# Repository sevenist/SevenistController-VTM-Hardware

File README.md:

# Sevenist Controller — Hardware (VTM)

Custom PCB for the **Sevenist Controller**, a 64-track MIDI CC control surface built around an [ESP32-S3 Zero](https://docs.waveshare.com/ESP32-S3-Zero).

This repository holds the KiCad project, schematics and fabrication files for the board. The code for it : [VTM Firmware repository](https://github.com/sevenist/SevenistController-VTM-Firmware).

> **Status: updated, should work but not tested yet. will upload soon some BOM file.**
> Fabricate at your own risk until it's confirmed working.

## Repository layout

```
relControll.kicad_pro / .kicad_sch / .kicad_pcb   KiCad 10 project, schematic, board
images/                                            Board renders
```

## License

Released under the [GPL-3.0](LICENSE) license.

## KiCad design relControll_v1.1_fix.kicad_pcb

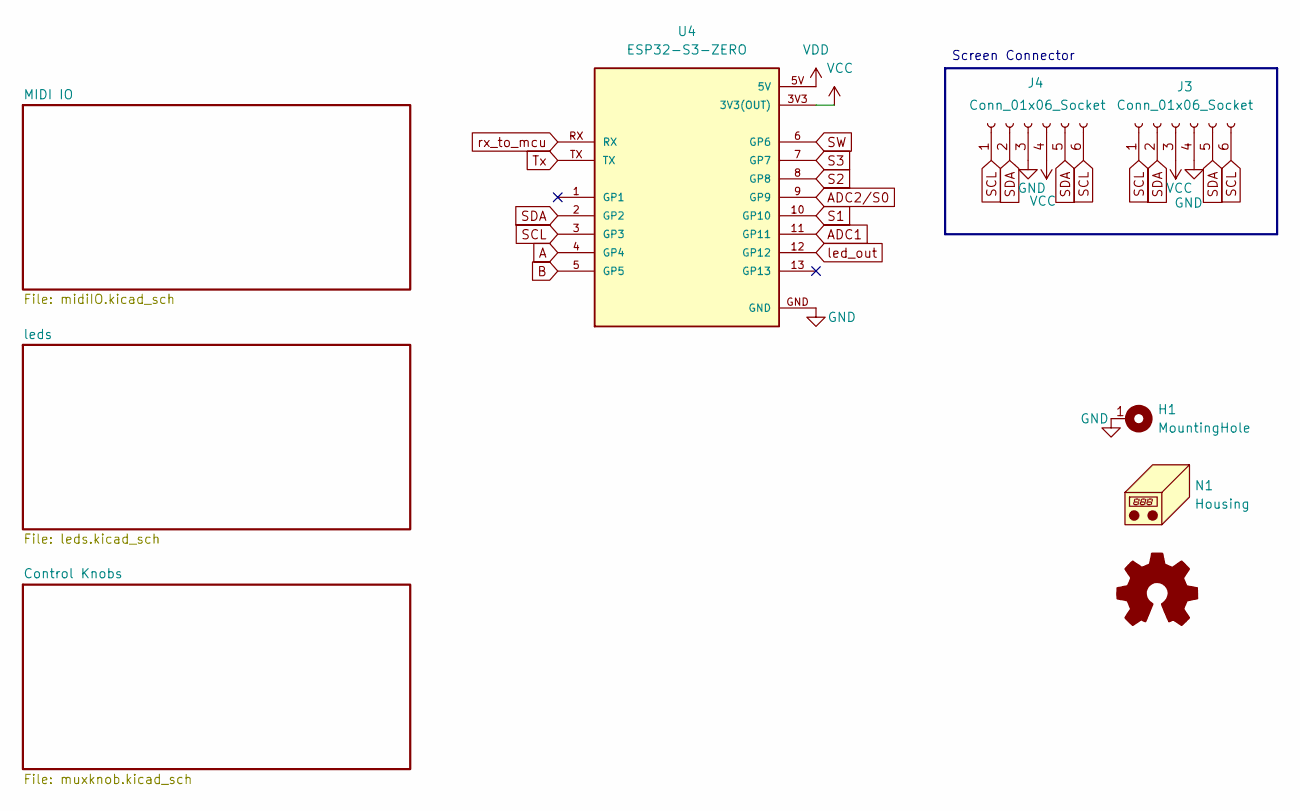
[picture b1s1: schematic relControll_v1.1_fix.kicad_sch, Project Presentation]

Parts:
H1: MountingHole; MountingHole_2.7mm_M2.5_ISO14580_Pad
J3, J4: Conn_01x06_Socket; PinSocket_1x06_P2.54mm_Vertical
N1: Housing; Screw_Generic_2.0x3.0mm_SilkScreen
U4: ESP32-S3-ZERO; MODULE_ESP32-S3-ZERO; PARTREV NA

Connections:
A: U4.4 (GP4); also elsewhere on the board
ADC1: U4.11 (GP11); also elsewhere on the board
ADC2/S0: U4.9 (GP9); also elsewhere on the board
B: U4.5 (GP5); also elsewhere on the board
GND: H1.1, J3.4, J4.3, U4.GND; also elsewhere on the board
S1: U4.10 (GP10); also elsewhere on the board
S2: U4.8 (GP8); also elsewhere on the board
S3: U4.7 (GP7); also elsewhere on the board
SCL: J3.1, J3.6, J4.1, J4.6, U4.3 (GP3)
SDA: J3.2, J3.5, J4.2, J4.5, U4.2 (GP2)
SW: U4.6 (GP6); also elsewhere on the board
Tx: U4.TX; also elsewhere on the board
VCC: J3.3, J4.4, U4.3V3 (3V3(OUT)); also elsewhere on the board
VDD: U4.5V; also elsewhere on the board
led_out: U4.12 (GP12); also elsewhere on the board
rx_to_mcu: U4.RX; also elsewhere on the board

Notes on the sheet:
Screen Connector

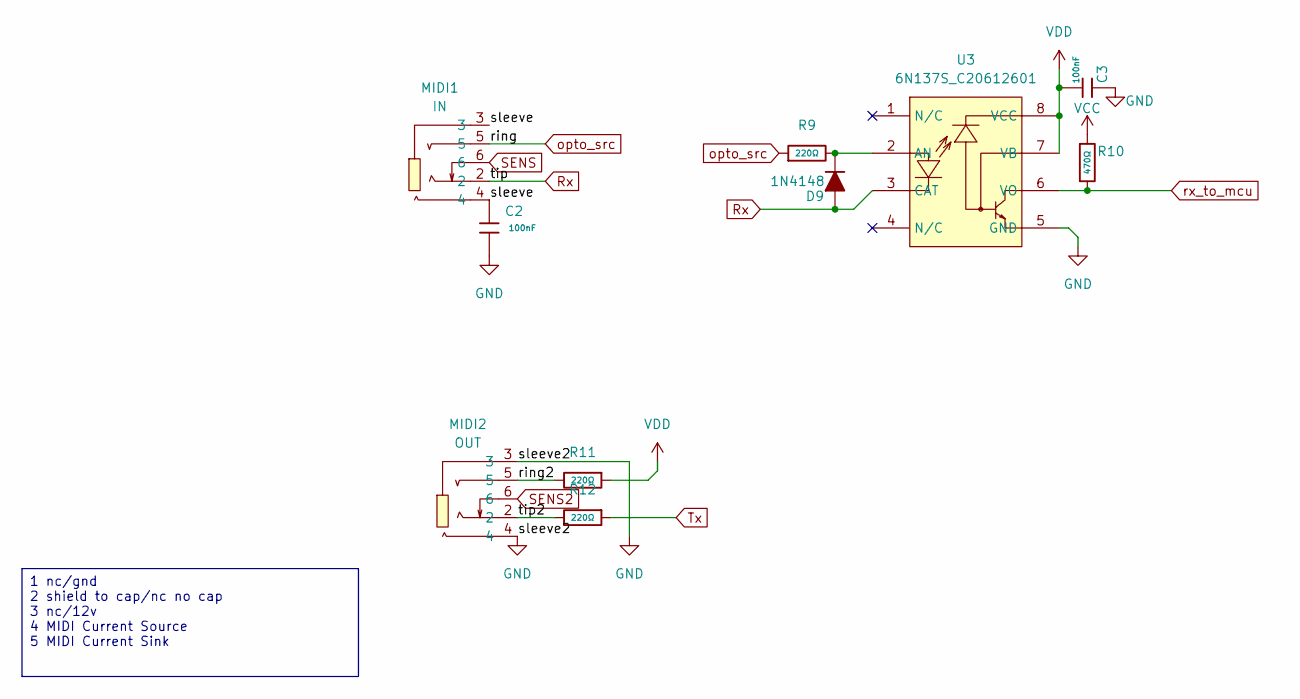
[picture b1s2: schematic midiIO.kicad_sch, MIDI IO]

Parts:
C2, C3: 100nF; C_0805; Voltage Rated 50V; Tolerance ±10%; Part CC0805KRX7R9BB104; LCSC C49678
D9: 1N4148; D_SOD123_axial
MIDI1: IN; AUDIO-TH_PJ-3270; MPN PJ-3270; LCSC Part C381134
MIDI2: OUT; AUDIO-TH_PJ-3270; MPN PJ-3270; LCSC Part C381134
R9, R11, R12: 220Ω; R_0805; Overload Voltage (Max) 150V; Tolerance ±1%; Part 0805W8F2200T5E; LCSC C17557
R10: 470Ω; R_0805; Overload Voltage (Max) 150V; Tolerance ±1%; Part 0805W8F4700T5E; LCSC C17710
U3: 6N137S_C20612601; SOP-8_6.605x9.655mm_P2.54mm; MPN 6N137S; LCSC Part C20612601

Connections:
/MIDI IO/ring2: MIDI2.5, R11.2
/MIDI IO/sleeve: C2.1, MIDI1.3, MIDI1.4
/MIDI IO/tip2: MIDI2.2, R12.2
GND: C2.2, C3.2, MIDI2.3, MIDI2.4, U3.5 (GND); also elsewhere on the board
unnamed: D9.1 (K), R9.2, U3.2 (AN)
Rx: D9.2 (A), MIDI1.2, U3.3 (CAT)
SENS: MIDI1.6
SENS2: MIDI2.6
Tx: R12.1; also elsewhere on the board
VCC: R10.1; also elsewhere on the board
VDD: C3.1, R11.1, U3.7 (VB), U3.8 (VCC); also elsewhere on the board
opto_src: MIDI1.5, R9.1
rx_to_mcu: R10.2, U3.6 (VO); also elsewhere on the board

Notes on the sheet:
1 nc/gnd 2 shield to cap/nc no cap 3 nc/12v 4 MIDI Current Source 5 MIDI Current Sink

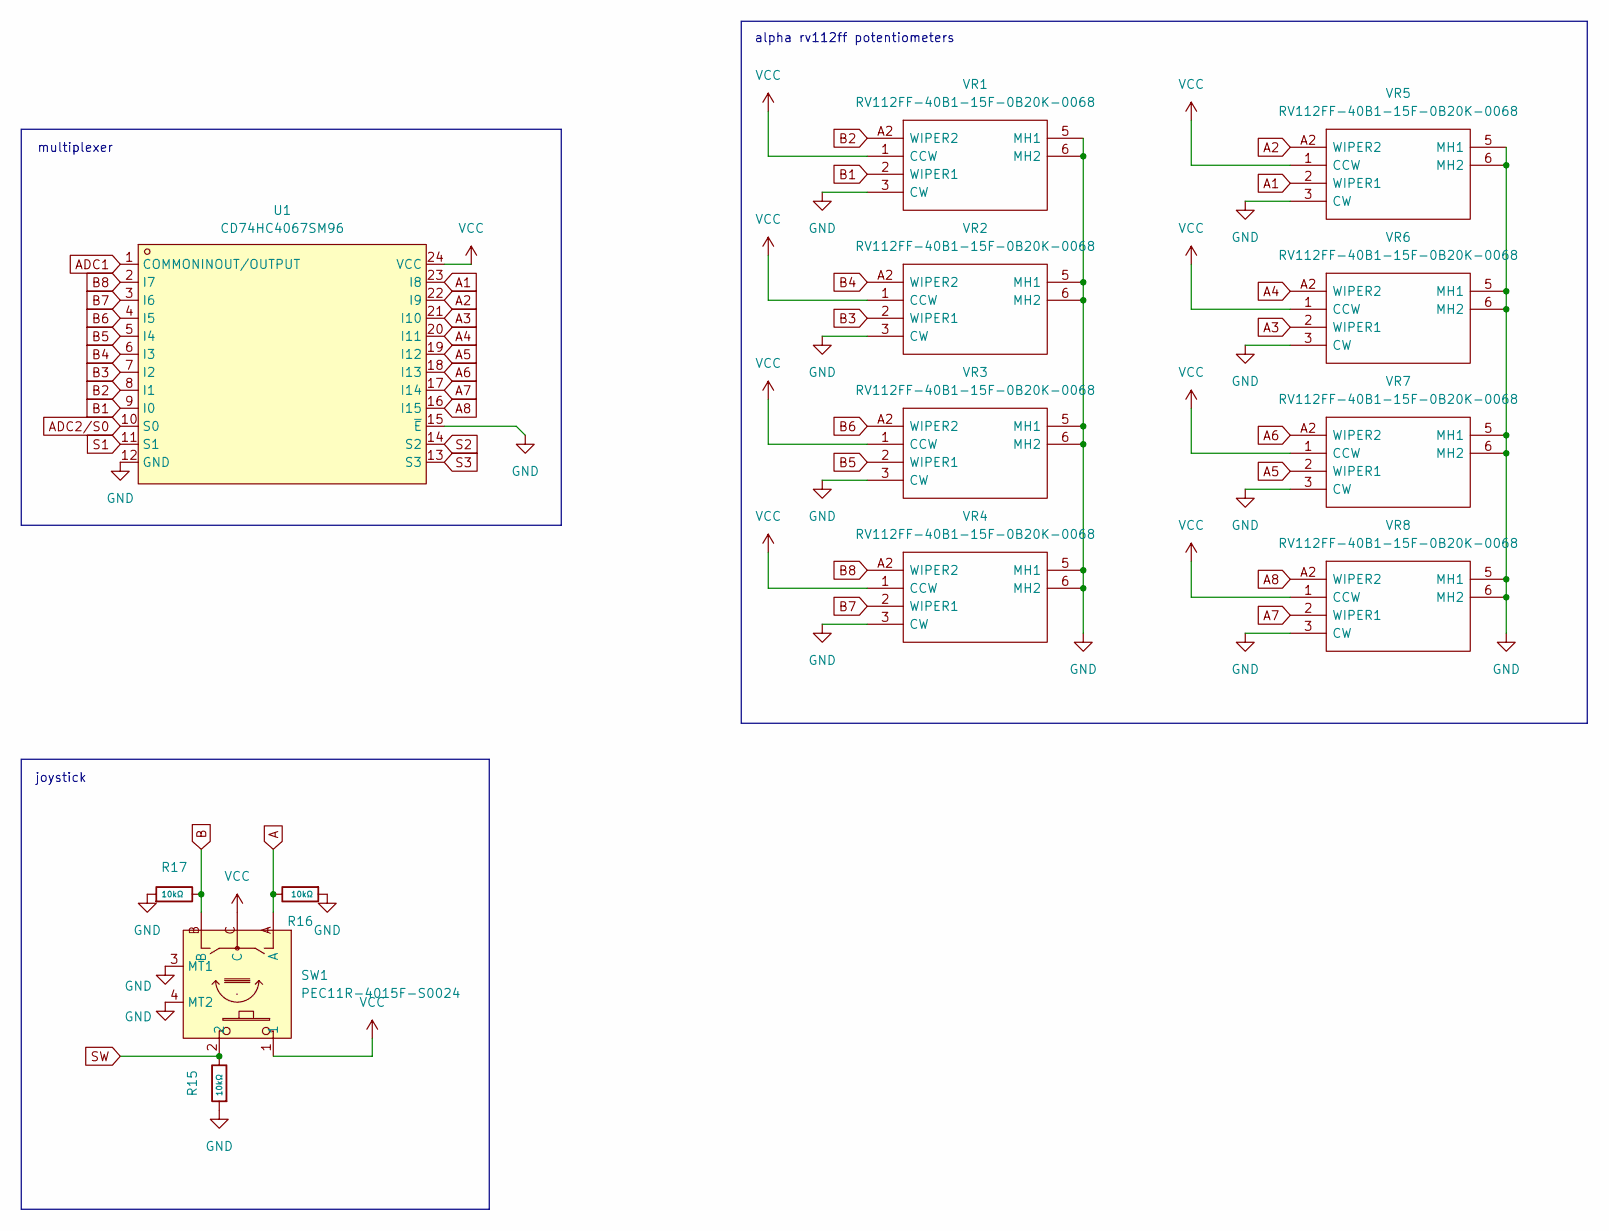
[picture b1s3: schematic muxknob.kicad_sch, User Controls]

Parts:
R15: 10kΩ; R0805; Overload Voltage (Max) 150V; Tolerance ±1%; Part 0805W8F1002T5E; LCSC C17414
R16, R17: 10kΩ; R_0805; Overload Voltage (Max) 150V; Tolerance ±1%; Part 0805W8F1002T5E; LCSC C17414
SW1: PEC11R-4015F-S0024; SW-TH_PEC12R-4130F-S0012; MPN PEC11R-4015F-S0024; LCSC Part C143789
U1: CD74HC4067SM96; SSOP-24_L8.1-W5.3-P0.65-LS7.8-BL; MPN CD74HC4067SM96; LCSC Part C98457
VR1, VR2, VR3, VR4, VR5, VR6, VR7, VR8: RV112FF-40B1-15F-0B20K-0068; RV112FF40B115F0B20K0068; Mouser Part Number 317-1240FF-15F-0B20K

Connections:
A: R16.2, SW1.A; also elsewhere on the board
A1: U1.23 (I8), VR5.2 (WIPER1)
A2: U1.22 (I9), VR5.A2 (WIPER2)
A3: U1.21 (I10), VR6.2 (WIPER1)
A4: U1.20 (I11), VR6.A2 (WIPER2)
A5: U1.19 (I12), VR7.2 (WIPER1)
A6: U1.18 (I13), VR7.A2 (WIPER2)
A7: U1.17 (I14), VR8.2 (WIPER1)
A8: U1.16 (I15), VR8.A2 (WIPER2)
ADC1: U1.1 (COMMONINOUT/OUTPUT); also elsewhere on the board
ADC2/S0: U1.10 (S0); also elsewhere on the board
B: R17.2, SW1.B; also elsewhere on the board
B1: U1.9 (I0), VR1.2 (WIPER1)
B2: U1.8 (I1), VR1.A2 (WIPER2)
B3: U1.7 (I2), VR2.2 (WIPER1)
B4: U1.6 (I3), VR2.A2 (WIPER2)
B5: U1.5 (I4), VR3.2 (WIPER1)
B6: U1.4 (I5), VR3.A2 (WIPER2)
B7: U1.3 (I6), VR4.2 (WIPER1)
B8: U1.2 (I7), VR4.A2 (WIPER2)
GND: R15.1, R16.1, R17.1, SW1.3 (MT1), SW1.4 (MT2), U1.12 (GND), U1.15 (~E), VR1.3 (CW), VR1.5 (MH1), VR1.6 (MH2), VR2.3 (CW), VR2.5 (MH1), VR2.6 (MH2), VR3.3 (CW), VR3.5 (MH1), VR3.6 (MH2), VR4.3 (CW), VR4.5 (MH1), VR4.6 (MH2), VR5.3 (CW), VR5.5 (MH1), VR5.6 (MH2), VR6.3 (CW), VR6.5 (MH1), VR6.6 (MH2), VR7.3 (CW), VR7.5 (MH1), VR7.6 (MH2), VR8.3 (CW), VR8.5 (MH1), VR8.6 (MH2); also elsewhere on the board
S1: U1.11 (S1); also elsewhere on the board
S2: U1.14 (S2); also elsewhere on the board
S3: U1.13 (S3); also elsewhere on the board
SW: R15.2, SW1.2; also elsewhere on the board
VCC: SW1.1, SW1.C, U1.24 (VCC), VR1.1 (CCW), VR2.1 (CCW), VR3.1 (CCW), VR4.1 (CCW), VR5.1 (CCW), VR6.1 (CCW), VR7.1 (CCW), VR8.1 (CCW); also elsewhere on the board

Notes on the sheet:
alpha rv112ff potentiometers
joystick
multiplexer

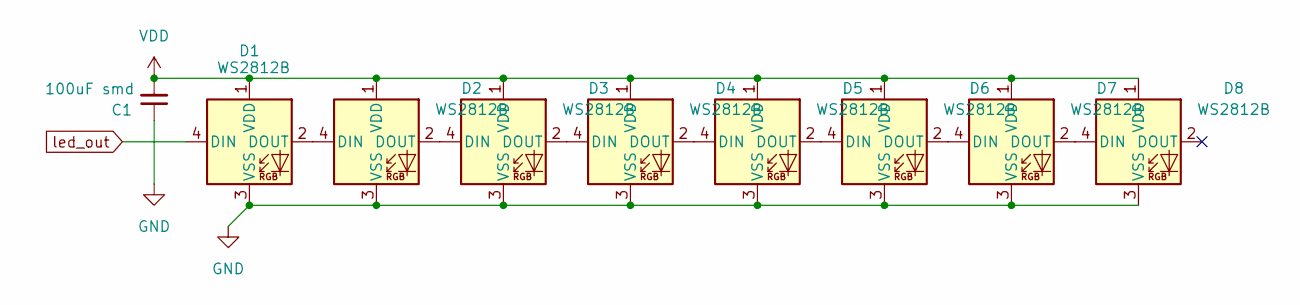
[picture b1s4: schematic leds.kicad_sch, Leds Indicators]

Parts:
C1: 100uF smd; C_Elec_6.3x5.4
D1, D2, D3, D4, D5, D6, D7, D8: WS2812B; LED_WS2812B_PLCC4_5.0x5.0mm_P3.2mm; LCSC C22461793

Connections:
GND: C1.1, D1.3 (VSS), D2.3 (VSS), D3.3 (VSS), D4.3 (VSS), D5.3 (VSS), D6.3 (VSS), D7.3 (VSS), D8.3 (VSS); also elsewhere on the board
unnamed: D1.2 (DOUT), D2.4 (DIN)
unnamed: D2.2 (DOUT), D3.4 (DIN)
unnamed: D3.2 (DOUT), D4.4 (DIN)
unnamed: D4.2 (DOUT), D5.4 (DIN)
unnamed: D5.2 (DOUT), D6.4 (DIN)
unnamed: D6.2 (DOUT), D7.4 (DIN)
unnamed: D7.2 (DOUT), D8.4 (DIN)
VDD: C1.2, D1.1 (VDD), D2.1 (VDD), D3.1 (VDD), D4.1 (VDD), D5.1 (VDD), D6.1 (VDD), D7.1 (VDD), D8.1 (VDD); also elsewhere on the board
led_out: D1.4 (DIN); also elsewhere on the board

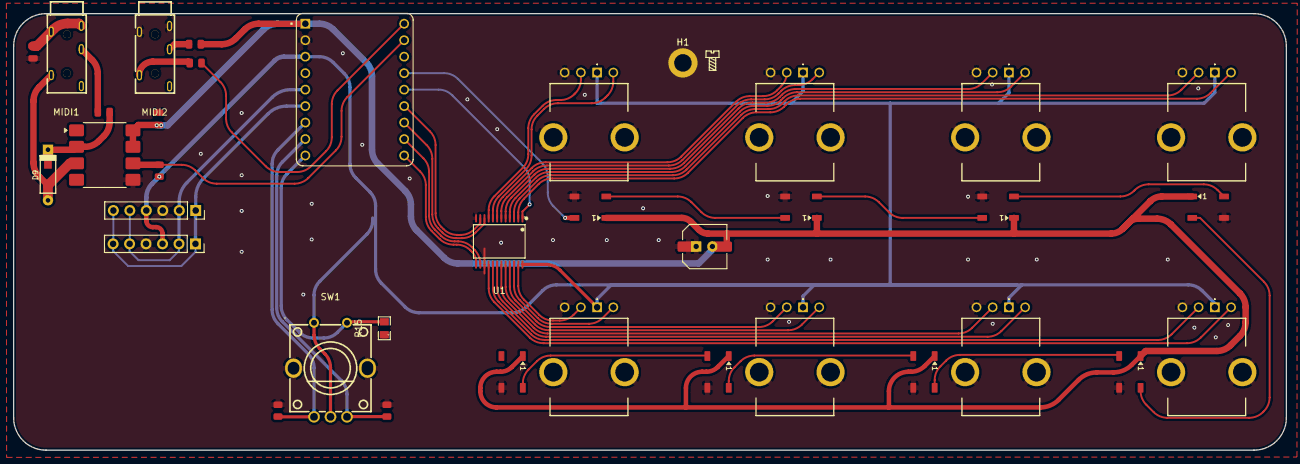
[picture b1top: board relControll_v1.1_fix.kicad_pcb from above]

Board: 2 copper layers, 196.2 x 67.3 mm, 38 parts (1 on the bottom side), 45 nets.

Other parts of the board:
C1#2: 100uF; CP_Radial_D7.5mm_P2.50mm

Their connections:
GND: C1#2.1; also elsewhere on the board
VDD: C1#2.2; also elsewhere on the board
